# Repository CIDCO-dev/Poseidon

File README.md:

# Poseidon
Hydrographic surveying platform operating system (ROS Noetic).

## Getting started (RPi4, Ubuntu 20.04, ROS Noetic)
- Clone under `/opt`: `sudo chown $USER:$USER /opt && cd /opt && git clone --recursive <repo>`
- Install: run `install/rpi4-noetic.sh` (RPi4 target).
- Build: `cd /opt/Poseidon/src/workspace && catkin_make -j1 -DCATKIN_BLACKLIST_PACKAGES="mavros;inertial_sense;velodyne;ins_piksi;velodyne_pointcloud;velodyne_driver;velodyne_laserscan;gnss_mosaic_x5;tf"`
- Source: `source /opt/ros/noetic/setup.bash` then `source /opt/Poseidon/src/workspace/devel/setup.bash`.
- Launch simulator: `roslaunch launch/Simulator/dummy_simulator_virtual-machine.launch`, then open the web UI at `http://localhost`.

## Docs
Full documentation lives in `doc/` (Markdown):
- `doc/README.md`: overview, build, run, tests
- `doc/install.md`: installation with dependencies (RPi4, Ubuntu 20.04, ROS Noetic)

## Tests
- C++/Python/ROS: `catkin_make run_tests -j1 -DCATKIN_BLACKLIST_PACKAGES="ins_piksi;libmavconn;echoboat_odometry;mavros_msgs;mavros;mavros_extras;test_mavros;gnss_mosaic_x5;imu_bno055;sonar_imagenex852;inertial_sense;raspberrypi_vitals;imu_null;sonar_dummy;gnss_dummy;lidar_filtering"`
- JS: `cd www/webroot/js && npm test --coverage`

## Tools
- Rosbag replay: `roslaunch launch/Echoboat/rosbag_replay.launch bag_filename:=rosbag.bag`
- Lidar georef: `./devel/lib/logger/lidarGeoreferencer -h` (supports filtering options)
- Logging modes: 1=Always ON, 2=Manual, 3=Speed based

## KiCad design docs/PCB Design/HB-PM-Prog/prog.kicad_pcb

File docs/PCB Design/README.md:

# Poseidon-PCB
PCBs for Poseidon Project

PCBs are design with Kicad 8.0

HB-HAT
HydroB HAT interface between RPI and devices

HB-BP
Power module bypass for Hydroblock

HB-PM
Power module for Hydroball

HB-HL
Led and hall interface module for Hydroball

HB-LED
Led PCB

HB-PM-Prog
Power Module Programmation Interface

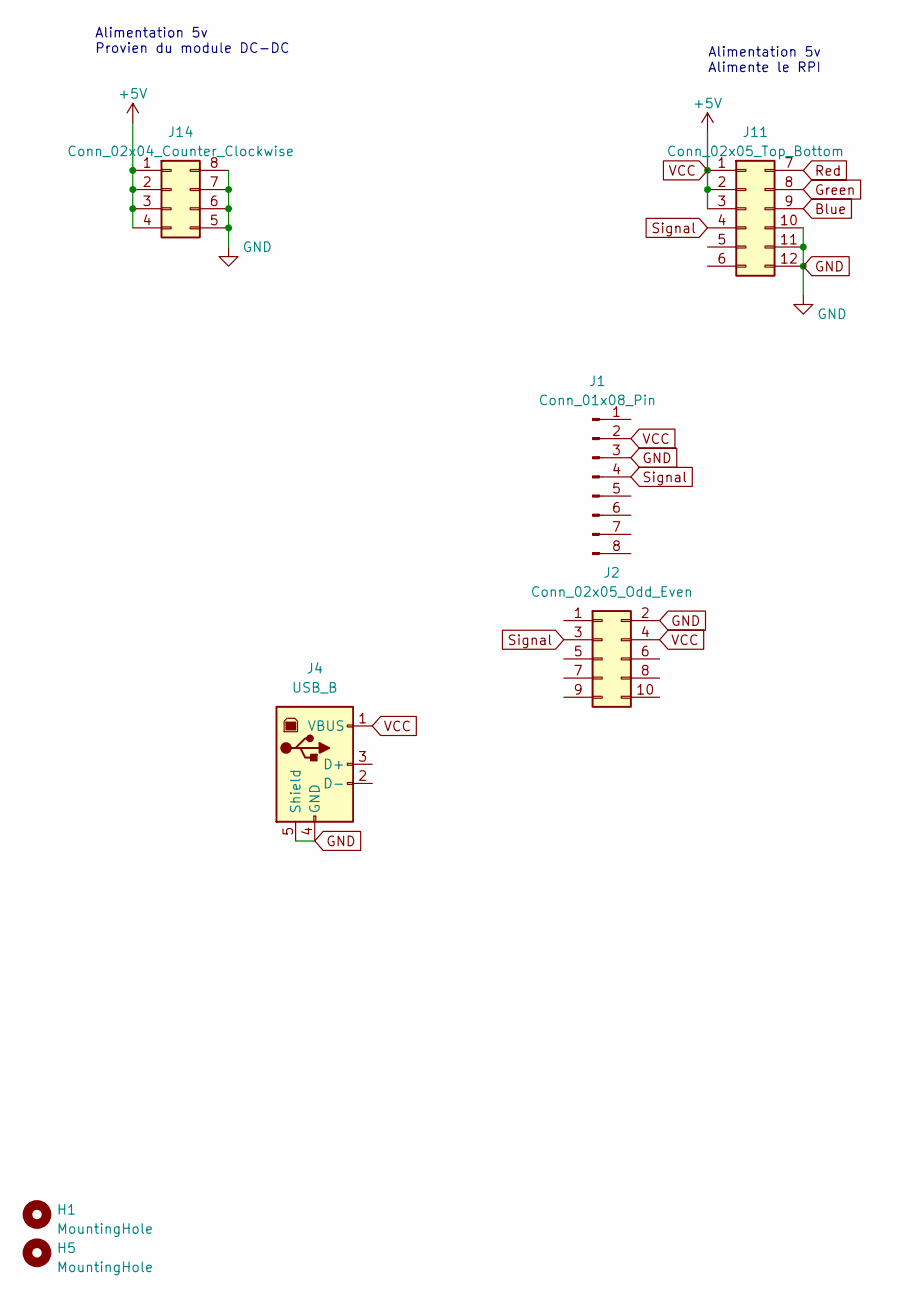
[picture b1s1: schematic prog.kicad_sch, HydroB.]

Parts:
H1, H5: MountingHole; MountingHole_2.7mm_M2.5_ISO7380_Pad
J1: Conn_01x08_Pin; PinHeader_1x08_P2.54mm_Horizontal
J2: Conn_02x05_Odd_Even; IDC-Header_2x05_P2.54mm_Vertical
J4: USB_B; USB_B_Lumberg_2411_02_Horizontal
J11: Conn_02x05_Top_Bottom; PinHeader_2x06_P2.54mm_Vertical
J14: Conn_02x04_Counter_Clockwise; PinHeader_2x04_P2.54mm_Vertical

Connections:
Blue: J11.9
GND: J1.3, J2.2, J4.4 (GND), J4.5 (Shield), J11.10, J11.11, J11.12, J14.5, J14.6, J14.7, J14.8
Green: J11.8
Red: J11.7
Signal: J1.4, J2.3, J11.4
VCC: J1.2, J2.4, J4.1 (VBUS), J11.1, J11.2, J11.3, J14.1, J14.2, J14.3, J14.4

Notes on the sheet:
Alimentation 5v Alimente le RPI
Alimentation 5v Provien du module DC-DC

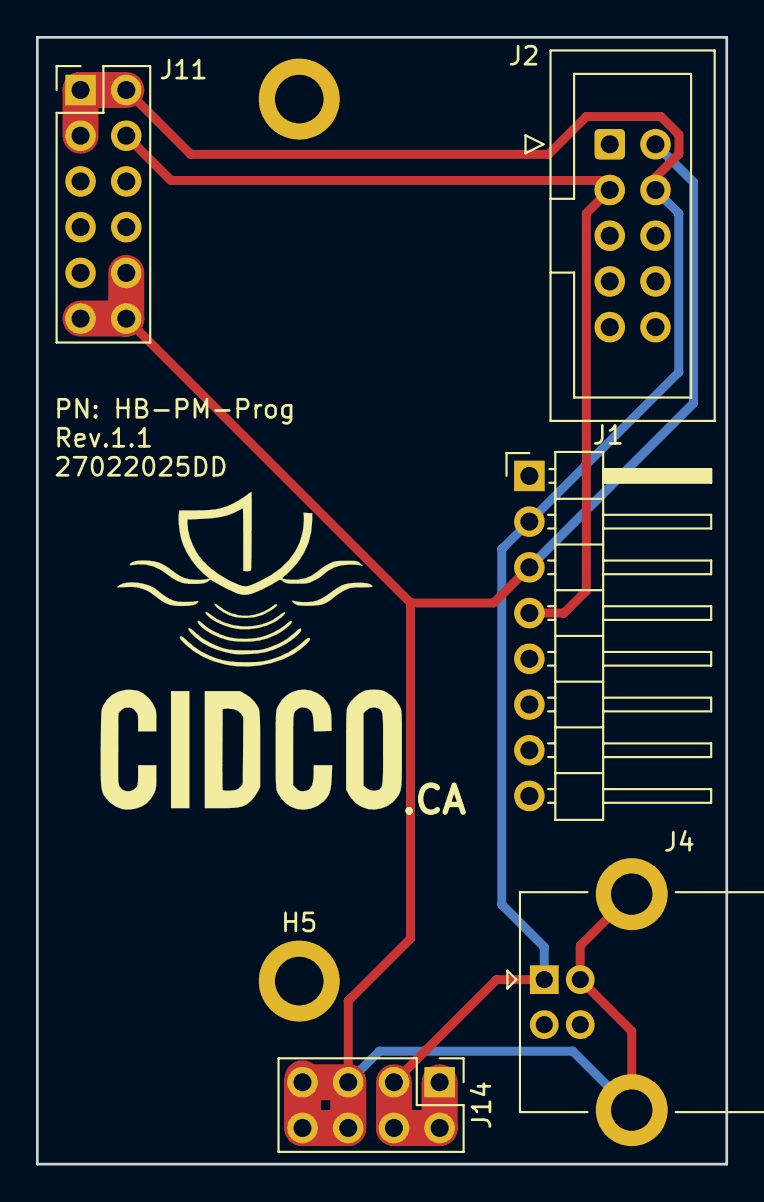
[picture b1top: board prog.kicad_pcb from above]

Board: 2 copper layers, 38.3 x 62.6 mm, 8 parts (0 on the bottom side), 3 nets.

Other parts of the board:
logo1: LOGO; logo cidco

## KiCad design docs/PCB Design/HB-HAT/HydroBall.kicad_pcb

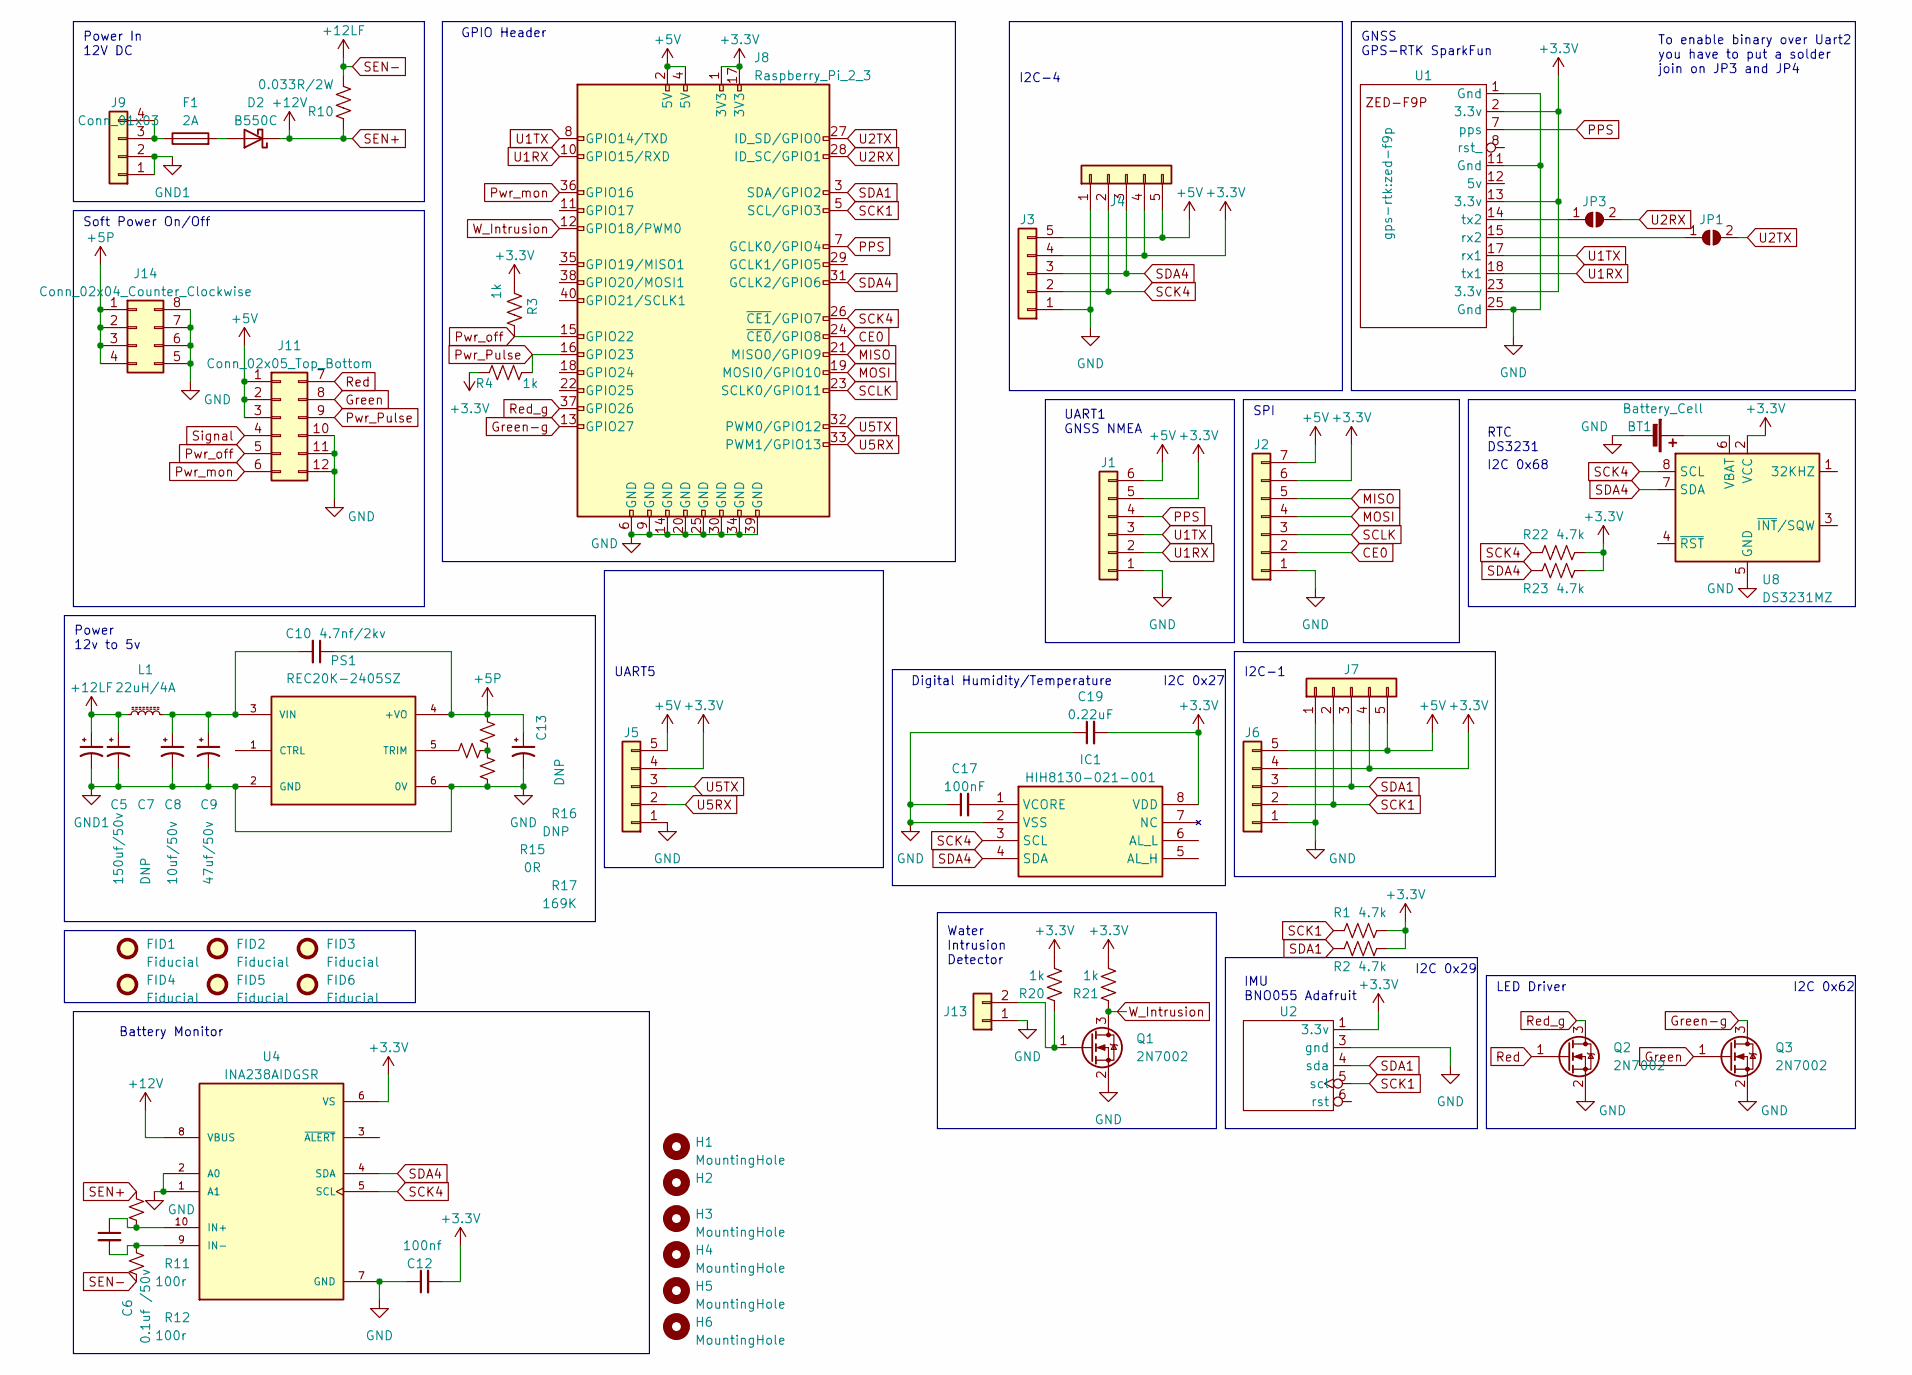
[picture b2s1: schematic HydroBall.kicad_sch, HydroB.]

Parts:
BT1: Battery_Cell; BatteryHolder_Keystone_1058_1x2032
C5: 150uf/50v; CP_Radial_D10.0mm_P5.00mm
C6: 0.1uf /50v; C_1206_3216Metric
C7: DNP; C_1206_3216Metric
C8: 10uf/50v; C_1206_3216Metric
C9: 47uf/50v; CP_Radial_D10.0mm_P5.00mm
C10: 4.7nf/2kv; C_1206_3216Metric
C12: 100nf; C_1206_3216Metric
C13: DNP; CP_Elec_6.3x9.9
C17: 100nF; C_1206_3216Metric
C19: 0.22uF; C_1206_3216Metric
D2: B550C; D_SMC
F1: 2A; Fuse_1206_3216Metric
FID1, FID2, FID3, FID4, FID5, FID6: Fiducial; Fiducial_0.75mm_Mask2.25mm
H1, H2, H3, H4, H5, H6: MountingHole; MountingHole_2.7mm_M2.5_ISO7380_Pad
IC1: HIH8130-021-001; SOIC127P600X206-8N; Mouser Part Number 785-HIH8130-021-001
J1: Conn_01x05; JST_XH_B6B-XH-AM_1x06_P2.50mm_Vertical
J2: Conn_01x07; JST_XH_B7B-XH-AM_1x07_P2.50mm_Vertical
J3, J4, J6, J7: Conn_01x05; JST_XH_B5B-XH-AM_1x05_P2.50mm_Vertical
J5: Conn_01x06; JST_XH_B5B-XH-AM_1x05_P2.50mm_Vertical
J8: Raspberry_Pi_2_3; PinSocket_2x20_P2.54mm_Vertical
J9: Conn_01x03; PhoenixContact_MSTBVA_2,5_4-G-5,08_1x04_P5.08mm_Vertical
J11: Conn_02x05_Top_Bottom; PinHeader_2x06_P2.54mm_Vertical
J13: Conn_01x06; JST_XH_B2B-XH-AM_1x02_P2.50mm_Vertical
J14: Conn_02x04_Counter_Clockwise; PinHeader_2x04_P2.54mm_Vertical
JP1, JP3: SolderJumper_2_Open; SolderJumper-2_P1.3mm_Open_RoundedPad1.0x1.5mm
L1: 22uH/4A; L_1210_3225Metric
PS1: REC20K-2405SZ; CONV_PDQE20-Q24-S5-D; PARTREV 1.0
Q1, Q2, Q3: 2N7002; SOT-23
R1, R2, R22, R23: 4.7k; R_1206_3216Metric
R3, R4, R20, R21: 1k; R_1206_3216Metric
R10: 0.033R/2W; R_2512_6332Metric
R11, R12: 100r; R_1206_3216Metric
R15: 0R; R_1206_3216Metric
R16: DNP; R_1206_3216Metric
R17: 169K; R_1206_3216Metric
U1: zed-f9p
U2: bno055
U4: INA238AIDGSR; SOP50P490X110-10N; PARTREV A
U8: DS3231MZ; SOIC-8_3.9x4.9mm_P1.27mm

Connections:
+3.3V: C12.2, C19.2, IC1.8 (VDD), J1.5, J2.6, J3.4, J4.4, J5.4, J6.4, J7.4, J8.1 (3V3), J8.17 (3V3), R1.2, R2.2, R3.2, R4.2, R20.2, R21.2, R22.2, R23.2, U1.2 (3.3v), U1.13 (3.3v), U1.23 (3.3v), U2.1 (3.3v), U4.6 (VS), U8.2 (VCC)
+5P: C10.1, C13.1, J14.1, J14.2, J14.3, J14.4, PS1.4 (+VO), R16.1
+5V: J1.6, J2.7, J3.5, J4.5, J5.5, J6.5, J7.5, J8.2 (5V), J8.4 (5V), J11.1, J11.2, J11.3
CE0: J2.2, J8.24 (~CE0/GPIO8)
GND: BT1.2 (-), C5.2, C7.2, C8.2, C9.2, C12.1, C13.2, C17.1, C19.1, IC1.2 (VSS), J1.1, J2.1, J3.1, J4.1, J5.1, J6.1, J7.1, J8.6 (GND), J8.9 (GND), J8.14 (GND), J8.20 (GND), J8.25 (GND), J8.30 (GND), J8.34 (GND), J8.39 (GND), J9.1, J9.2, J11.10, J11.11, J11.12, J13.1, J14.5, J14.6, J14.7, J14.8, PS1.2 (GND), PS1.6 (0V), Q1.2 (S), Q2.2 (S), Q3.2 (S), R17.2, U1.1 (Gnd), U1.11 (Gnd), U1.25 (Gnd), U2.3 (gnd), U4.1 (A1), U4.2 (A0), U4.7 (GND), U8.5 (GND)
Green: J11.8, Q3.1 (G)
Green-g: J8.13 (GPIO27), Q3.3 (D)
MISO: J2.5, J8.21 (MISO0/GPIO9)
MOSI: J2.4, J8.19 (MOSI0/GPIO10)
unnamed: BT1.1 (+), U8.6 (VBAT)
unnamed: D2.2 (A), F1.2
unnamed: C17.2, IC1.1 (VCORE)
unnamed: F1.1, J9.3, J9.4
unnamed: J13.2, Q1.1 (G), R20.1
unnamed: JP1.1 (A), U1.15 (rx2)
unnamed: JP3.1 (A), U1.14 (tx2)
unnamed: PS1.5 (TRIM), R15.1
unnamed: C8.1, C9.1, C10.2, L1.2, PS1.3 (VIN)
unnamed: R15.2, R16.2, R17.1
unnamed: C6.1, R11.2, U4.10 (IN+)
unnamed: C6.2, R12.1, U4.9 (IN-)
PPS: J1.4, J8.7 (GCLK0/GPIO4), U1.7 (pps)
Pwr_Pulse: J8.16 (GPIO23), J11.9, R4.1
Pwr_mon: J8.36 (GPIO16), J11.6
Pwr_off: J8.15 (GPIO22), J11.5, R3.1
Red: J11.7, Q2.1 (G)
Red_g: J8.37 (GPIO26), Q2.3 (D)
SCK1: J6.2, J7.2, J8.5 (SCL/GPIO3), R1.1, U2.5 (scl)
SCK4: IC1.3 (SCL), J3.2, J4.2, J8.26 (~CE1/GPIO7), R22.1, U4.5 (SCL), U8.8 (SCL)
SCLK: J2.3, J8.23 (SCLK0/GPIO11)
SDA1: J6.3, J7.3, J8.3 (SDA/GPIO2), R2.1, U2.4 (sda)
SDA4: IC1.4 (SDA), J3.3, J4.3, J8.31 (GCLK2/GPIO6), R23.1, U4.4 (SDA), U8.7 (SDA)
SEN+: D2.1 (K), R10.1, R11.1, U4.8 (VBUS)
SEN-: C5.1, C7.1, L1.1, R10.2, R12.2
Signal: J11.4
U1RX: J1.2, J8.10 (GPIO15/RXD), U1.18 (tx1)
U1TX: J1.3, J8.8 (GPIO14/TXD), U1.17 (rx1)
U2RX: J8.28 (ID_SC/GPIO1), JP3.2 (B)
U2TX: J8.27 (ID_SD/GPIO0), JP1.2 (B)
U5RX: J5.2, J8.33 (PWM1/GPIO13)
U5TX: J5.3, J8.32 (PWM0/GPIO12)
W_Intrusion: J8.12 (GPIO18/PWM0), Q1.3 (D), R21.1

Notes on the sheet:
SPI
Water Intrusion Detector
I2C 0x68
Soft Power On/Off
Battery Monitor
GPIO Header
I2C 0x29
I2C-1
LED Driver
Power In 12V DC
I2C 0x27
RTC DS3231
GNSS GPS-RTK SparkFun
I2C 0x62
To enable binary over Uart2 you have to put a solder join on JP3 and JP4
UART5
Power 12v to 5v
I2C-4
IMU BNO055 Adafruit
Digital Humidity/Temperature
UART1 GNSS NMEA

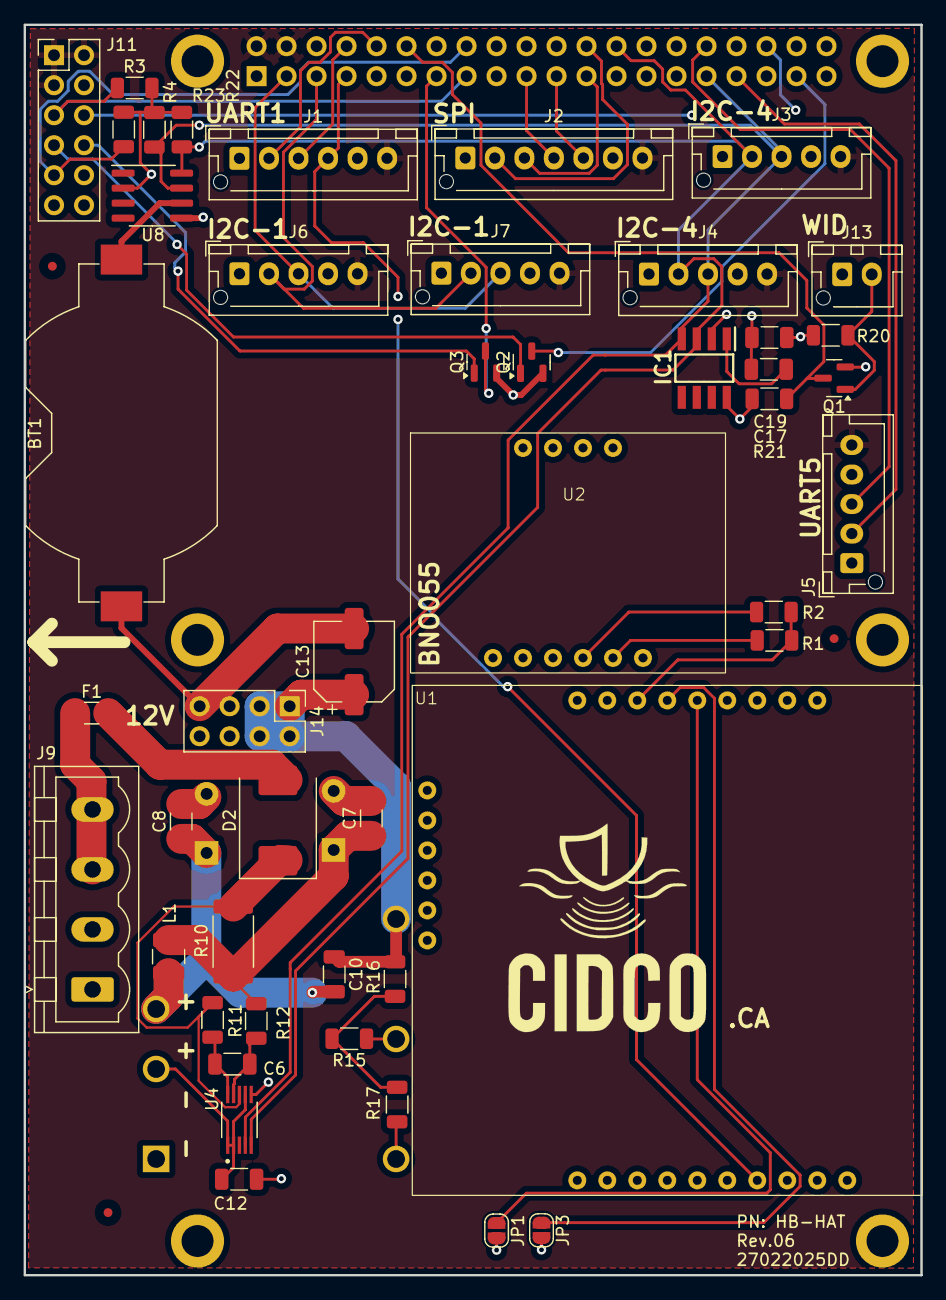
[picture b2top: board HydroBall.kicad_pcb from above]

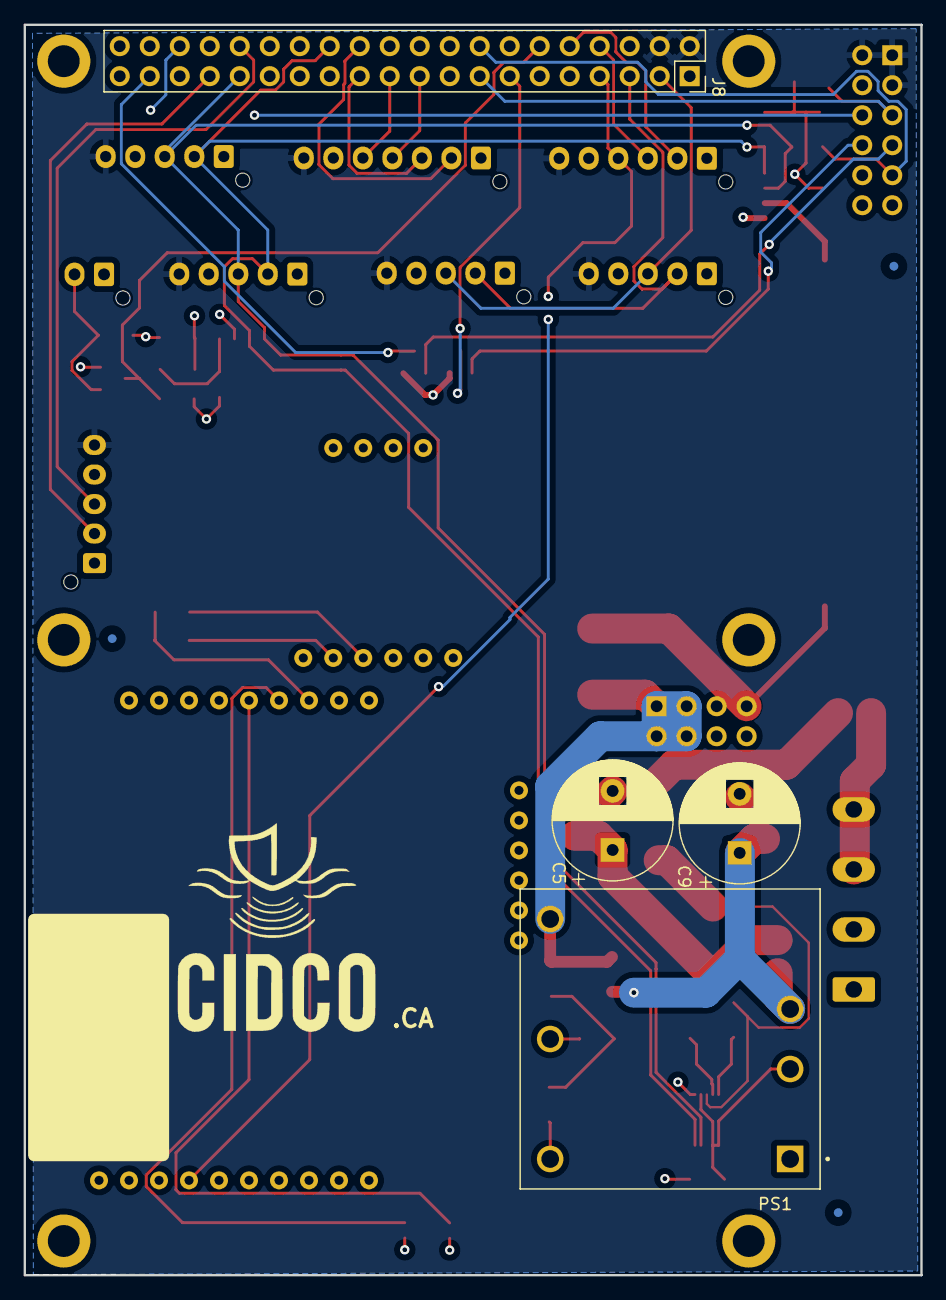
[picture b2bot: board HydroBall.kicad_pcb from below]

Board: 4 copper layers, 75.9 x 105.9 mm, 65 parts (8 on the bottom side), 41 nets.

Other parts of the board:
logo1, logo1#2: LOGO; logo cidco

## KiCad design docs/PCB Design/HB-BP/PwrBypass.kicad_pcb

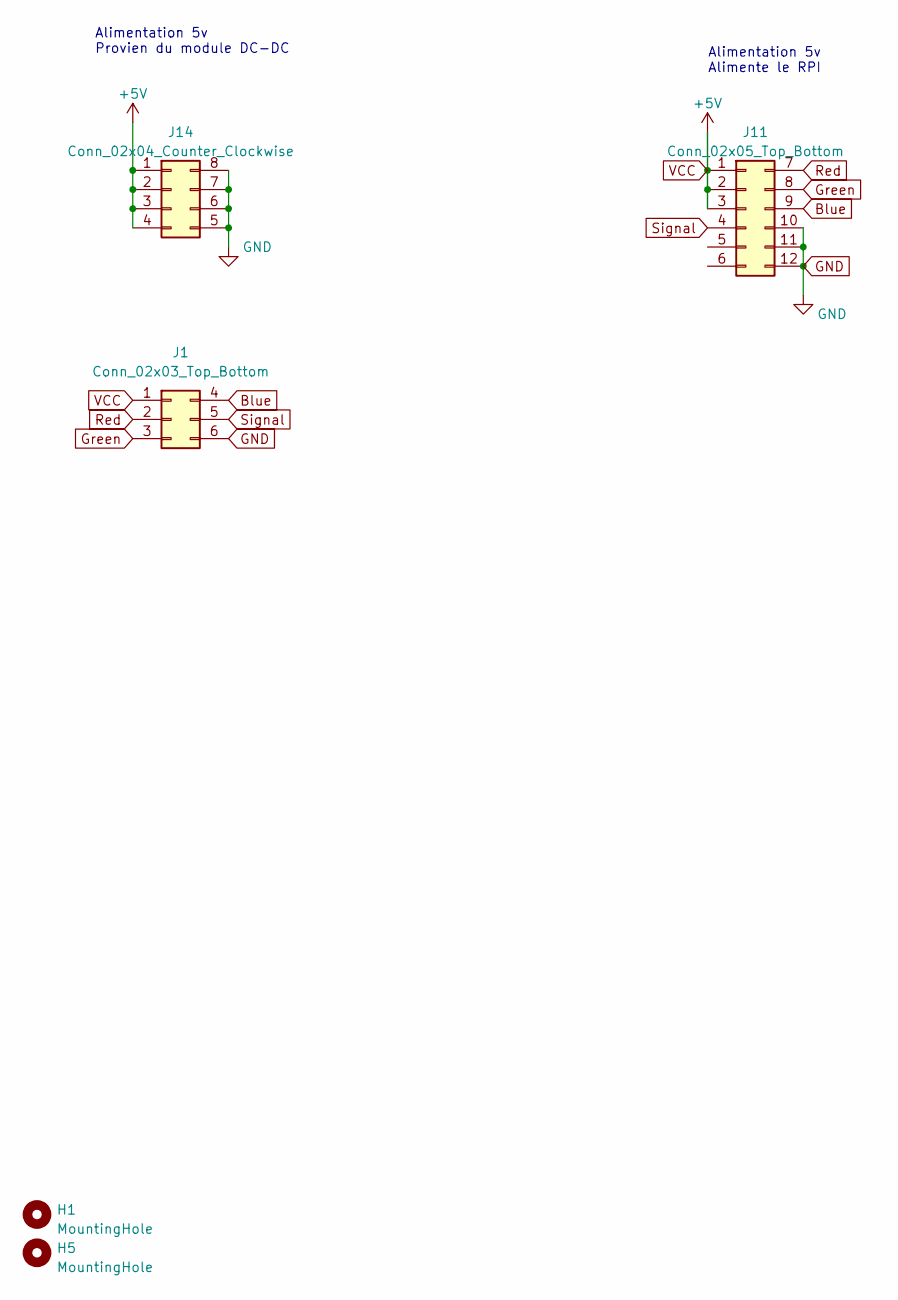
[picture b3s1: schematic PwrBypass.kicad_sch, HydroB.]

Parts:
H1, H5: MountingHole; MountingHole_2.7mm_M2.5_ISO7380_Pad
J1: Conn_02x03_Top_Bottom; IDC-Header_2x03_P2.54mm_Vertical
J11: Conn_02x05_Top_Bottom; PinHeader_2x06_P2.54mm_Vertical
J14: Conn_02x04_Counter_Clockwise; PinHeader_2x04_P2.54mm_Vertical

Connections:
Blue: J1.4, J11.9
GND: J1.6, J11.10, J11.11, J11.12, J14.5, J14.6, J14.7, J14.8
Green: J1.3, J11.8
Red: J1.2, J11.7
Signal: J1.5, J11.4
VCC: J1.1, J11.1, J11.2, J11.3, J14.1, J14.2, J14.3, J14.4

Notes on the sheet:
Alimentation 5v Alimente le RPI
Alimentation 5v Provien du module DC-DC

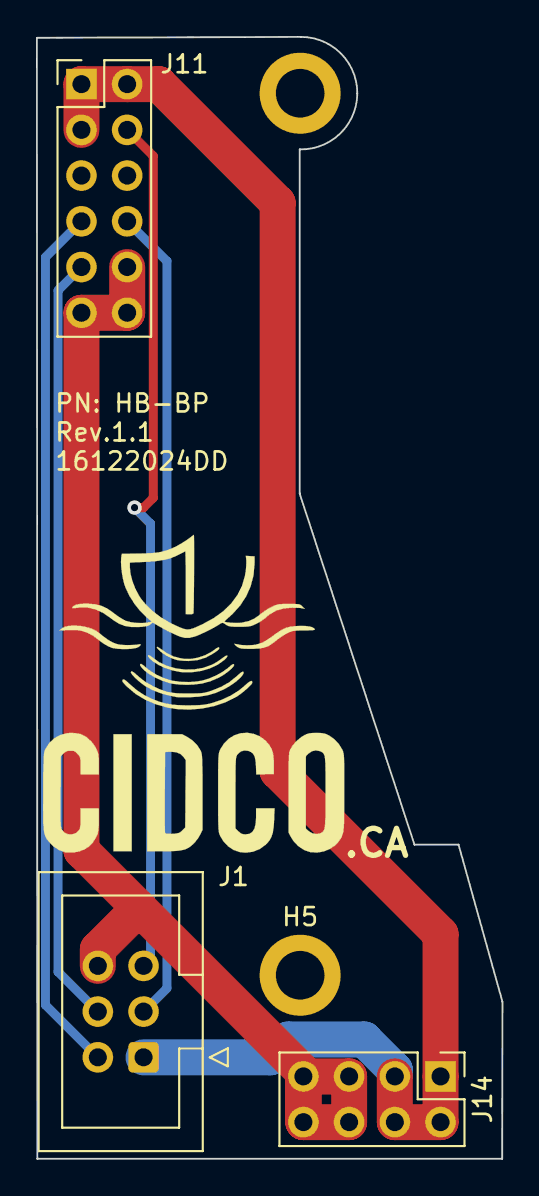
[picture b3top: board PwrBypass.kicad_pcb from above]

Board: 2 copper layers, 25.9 x 62.3 mm, 6 parts (0 on the bottom side), 6 nets.

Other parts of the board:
logo1: LOGO; logo cidco

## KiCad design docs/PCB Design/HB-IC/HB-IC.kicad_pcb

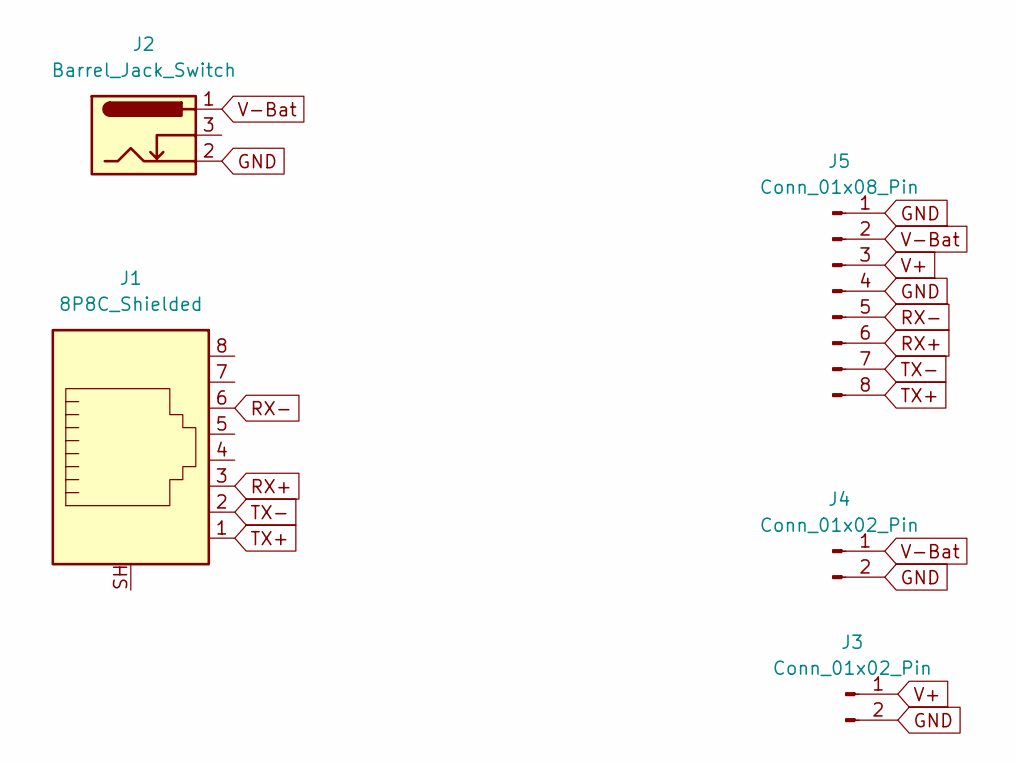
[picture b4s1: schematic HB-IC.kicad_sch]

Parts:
J1: 8P8C_Shielded; RJ45_HALO_HFJ11-x2450HRL_Horizontal
J2: Barrel_Jack_Switch; BarrelJack_Kycon_KLDX-0202-xC_Horizontal
J3: Conn_01x02_Pin; PhoenixContact_MSTBVA_2,5_2-G-5,08_1x02_P5.08mm_Vertical
J4: Conn_01x02_Pin
J5: Conn_01x08_Pin; PhoenixContact_MSTBVA_2,5_8-G-5,08_1x08_P5.08mm_Vertical

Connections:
GND: J2.2, J3.2, J4.2, J5.1, J5.4
RX+: J1.3, J5.6
RX-: J1.6, J5.5
TX+: J1.1, J5.8
TX-: J1.2, J5.7
V+: J3.1, J5.3
V-Bat: J2.1, J4.1, J5.2

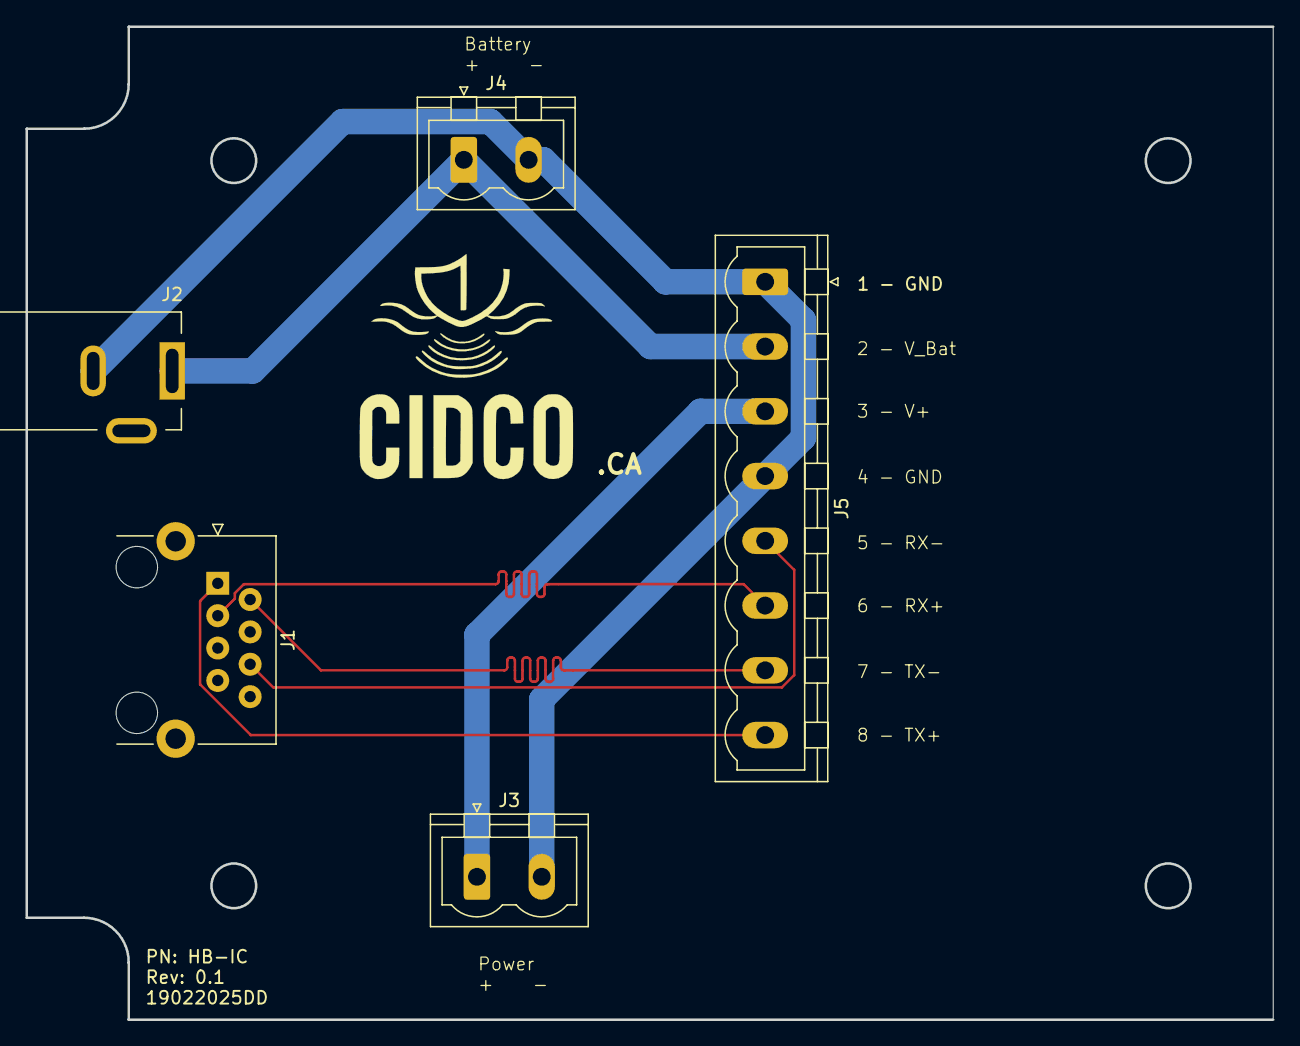
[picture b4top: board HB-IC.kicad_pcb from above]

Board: 2 copper layers, 97.8 x 77.9 mm, 6 parts (0 on the bottom side), 7 nets.

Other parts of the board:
logo1: LOGO; logo cidco

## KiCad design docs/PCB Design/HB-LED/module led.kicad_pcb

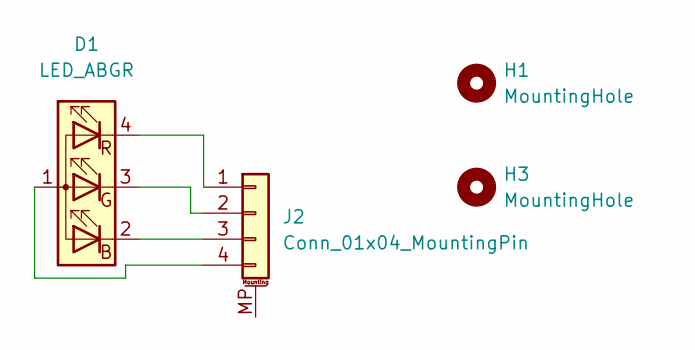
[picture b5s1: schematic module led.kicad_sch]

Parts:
D1: LED_ABGR; LED_D5.0mm-4_RGB
H1, H3: MountingHole; MountingHole_4.3mm_M4
J2: Conn_01x04_MountingPin; TE_84952-4_1x04-1MP_P1.0mm_Horizontal

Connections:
unnamed: D1.1 (A), J2.4
unnamed: D1.2 (BK), J2.3
unnamed: D1.3 (GK), J2.2
unnamed: D1.4 (RK), J2.1

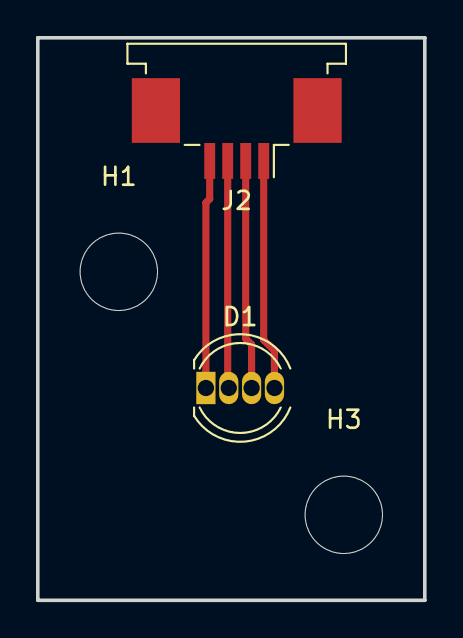
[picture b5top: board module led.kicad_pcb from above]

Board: 2 copper layers, 21.5 x 31.2 mm, 5 parts (1 on the bottom side), 4 nets.

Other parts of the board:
logo1: LOGO; logo cidco

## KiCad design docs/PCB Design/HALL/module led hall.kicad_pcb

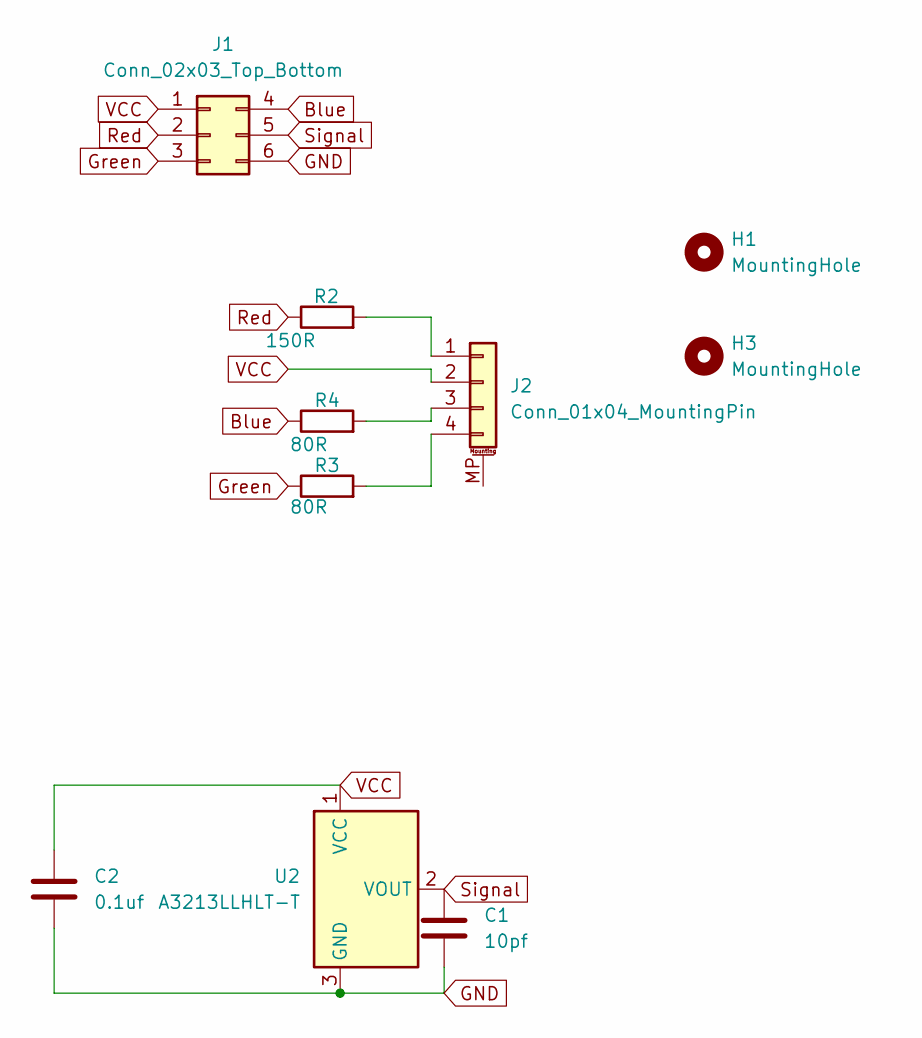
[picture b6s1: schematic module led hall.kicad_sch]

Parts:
C1: 10pf; C_1206_3216Metric
C2: 0.1uf; C_1206_3216Metric
H1, H3: MountingHole; MountingHole_4.3mm_M4
J1: Conn_02x03_Top_Bottom; IDC-Header_2x03_P2.54mm_Vertical
J2: Conn_01x04_MountingPin; TE_84952-4_1x04-1MP_P1.0mm_Horizontal
R2: 150R; R_1206_3216Metric
R3, R4: 80R; R_1206_3216Metric
U2: A3213LLHLT-T; SOT-23W

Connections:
Blue: J1.4, R4.1
GND: C1.2, C2.2, J1.6, U2.3 (GND)
Green: J1.3, R3.1
unnamed: J2.1, R2.2
unnamed: J2.3, R4.2
unnamed: J2.4, R3.2
Red: J1.2, R2.1
Signal: C1.1, J1.5, U2.2 (VOUT)
VCC: C2.1, J1.1, J2.2, U2.1 (VCC)

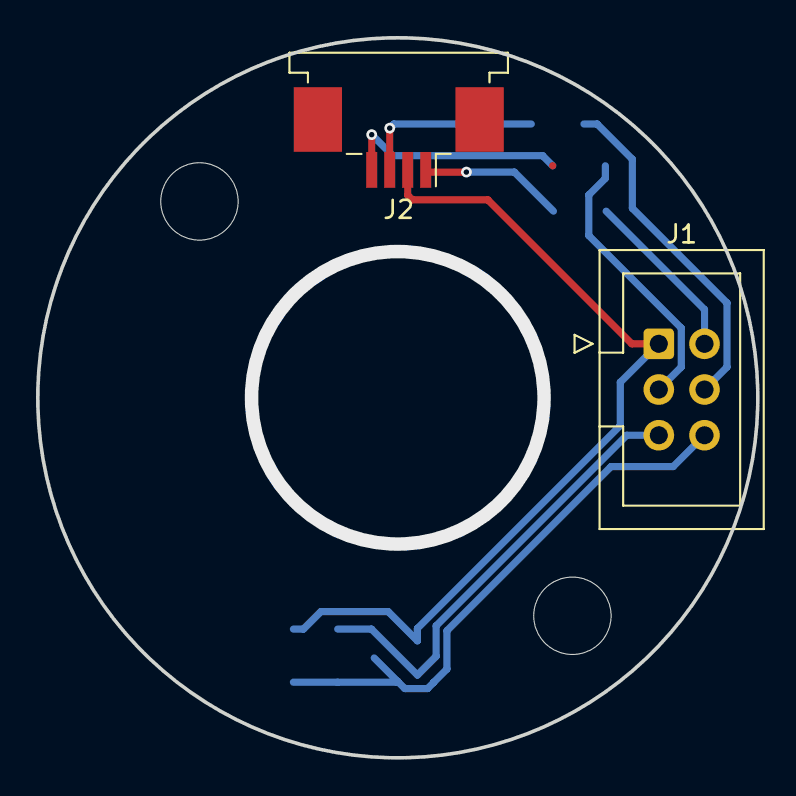
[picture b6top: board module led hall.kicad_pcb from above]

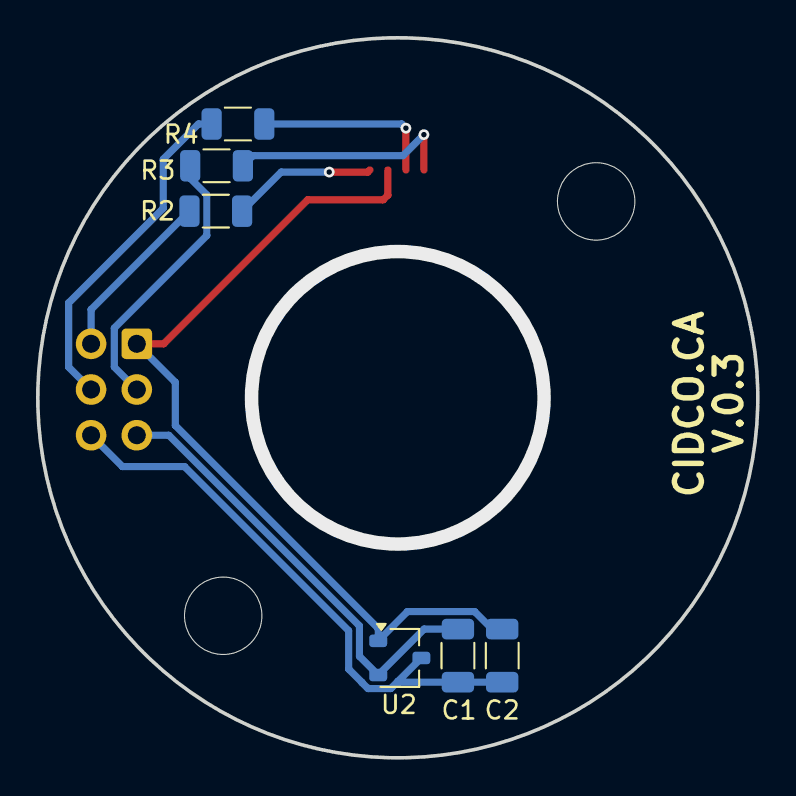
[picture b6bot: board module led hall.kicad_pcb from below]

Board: 4 copper layers, 40.0 x 40.0 mm, 10 parts (6 on the bottom side), 9 nets.

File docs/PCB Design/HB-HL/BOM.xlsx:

Comment | Designator | Footprint | JLCPCB Part #（optional）
Conn_01x04_MountingPin | J2 | TE_84952-4_1x04-1MP_P1.0mm_Horizontal | C262731
80R | R3,R4 | R_1206_3216Metric | C270896
10pf | C1 | C_1206_3216Metric | C377016
150R | R2 | R_1206_3216Metric | C2907432
A3213LLHLT-T | U2 | SOT-23W | C75884
0.1uf | C2 | C_1206_3216Metric | C841554

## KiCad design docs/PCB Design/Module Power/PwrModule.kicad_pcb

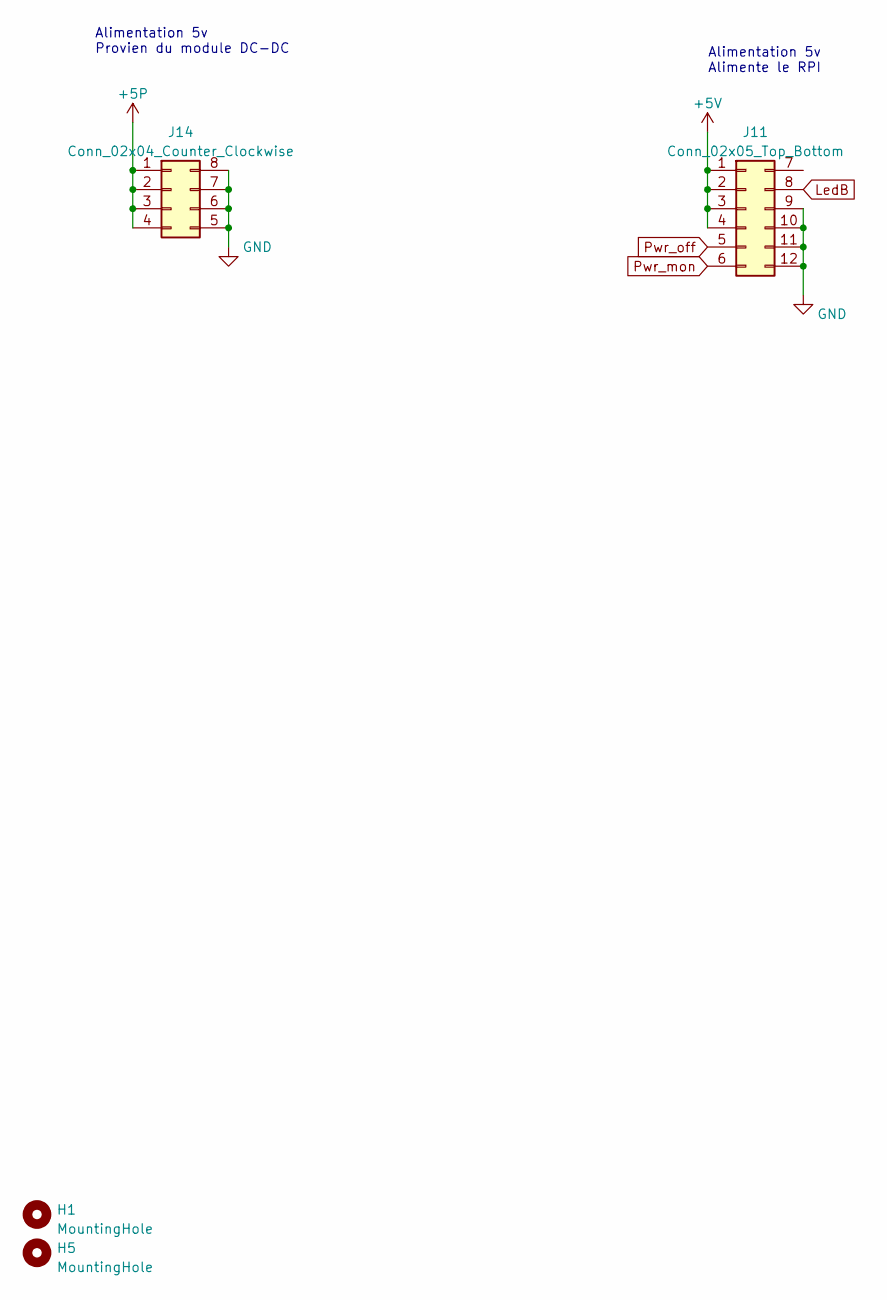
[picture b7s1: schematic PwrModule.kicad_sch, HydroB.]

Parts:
H1, H5: MountingHole; MountingHole_2.7mm_M2.5_ISO7380_Pad
J11: Conn_02x05_Top_Bottom; PinHeader_2x06_P2.54mm_Vertical
J14: Conn_02x04_Counter_Clockwise; PinHeader_2x04_P2.54mm_Vertical

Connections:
+5P: J14.1, J14.2, J14.3, J14.4
+5V: J11.1, J11.2, J11.3, J11.4
GND: J11.9, J11.10, J11.11, J11.12, J14.5, J14.6, J14.7, J14.8
LedB: J11.8
Pwr_mon: J11.6
Pwr_off: J11.5

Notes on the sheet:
Alimentation 5v Alimente le RPI
Alimentation 5v Provien du module DC-DC

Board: 4 copper layers, 4 parts (2 on the bottom side), 3 nets, no tracks yet.
